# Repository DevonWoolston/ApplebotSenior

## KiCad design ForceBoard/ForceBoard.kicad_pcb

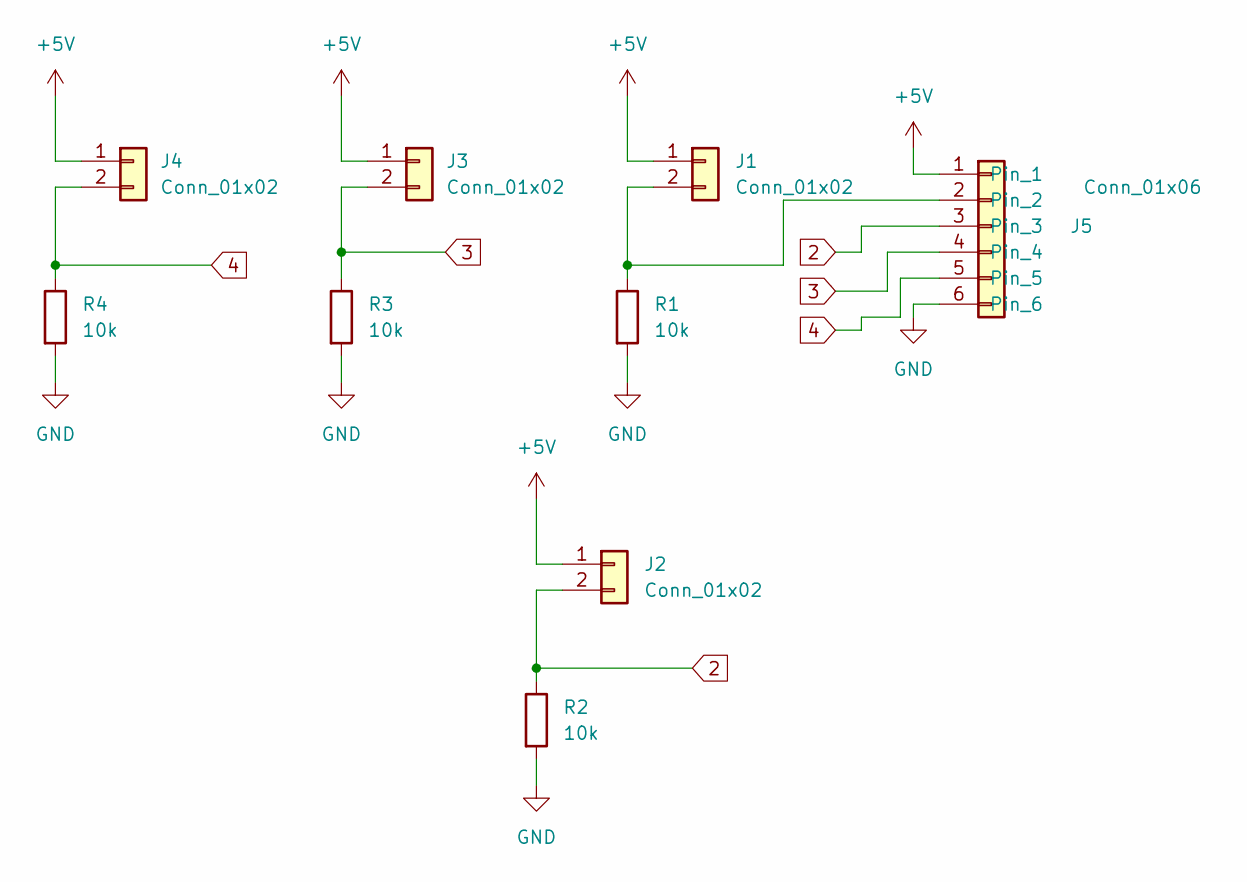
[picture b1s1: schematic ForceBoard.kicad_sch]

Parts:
J1, J2, J3, J4: Conn_01x02; JST_PH_B2B-PH-K_1x02_P2.00mm_Vertical
J5: Conn_01x06; JST_EH_B6B-EH-A_1x06_P2.50mm_Vertical
R1, R2, R3, R4: 10k; R_0805_2012Metric

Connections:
2: J2.2, J5.3, R2.1
3: J3.2, J5.4, R3.1
4: J4.2, J5.5, R4.1
+5V: J1.1, J2.1, J3.1, J4.1, J5.1
GND: J5.6, R1.2, R2.2, R3.2, R4.2
unnamed: J1.2, J5.2, R1.1

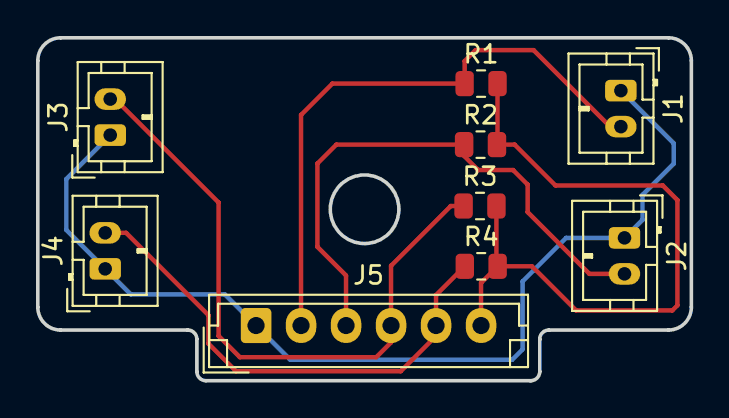
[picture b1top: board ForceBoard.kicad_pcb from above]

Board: 2 copper layers, 36.3 x 19.0 mm, 9 parts (0 on the bottom side), 6 nets.

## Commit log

2024-06-27 Your commit message
